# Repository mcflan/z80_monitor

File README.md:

# Z80 Monitor

</img>

A device that allows a host PC to read and write memory on the bus of a Z80
computer (or potentially other CPUs) as well as a few other functions. It makes
use of the Z80's BUSRQ / BUSAK feature to gain access to the bus while the CPU
is running. The circuit is based on an Atmel atmega1281. The host interface is
a bidirectional TTL-level serial (UART) connection that uses a simple hex-based
protocol to control the monitor and provide handshaking. The host interface is
electrically isolated to allow the target device to be power-cycled properly
without being back-powered by the serial signals. This also avoids any risk of
SCR latch-up.

## Host Connector

This is 6-way single-row header to fit a standard FTDI FT232 serial cable (TTL type.) It will work with the 5V and 3V3 versions.

 | Number | Function      |
 |:------:|:------------- |
 |  6     | Not Used      |
 |  5     | Serial Out    |
 |  4     | Serial In     |
 |  3     | Power In      |
 |  2     | Not Used      |
 |  1     | Ground        |

## Bus Connector

See the [pinout file](bus_pinout.md)

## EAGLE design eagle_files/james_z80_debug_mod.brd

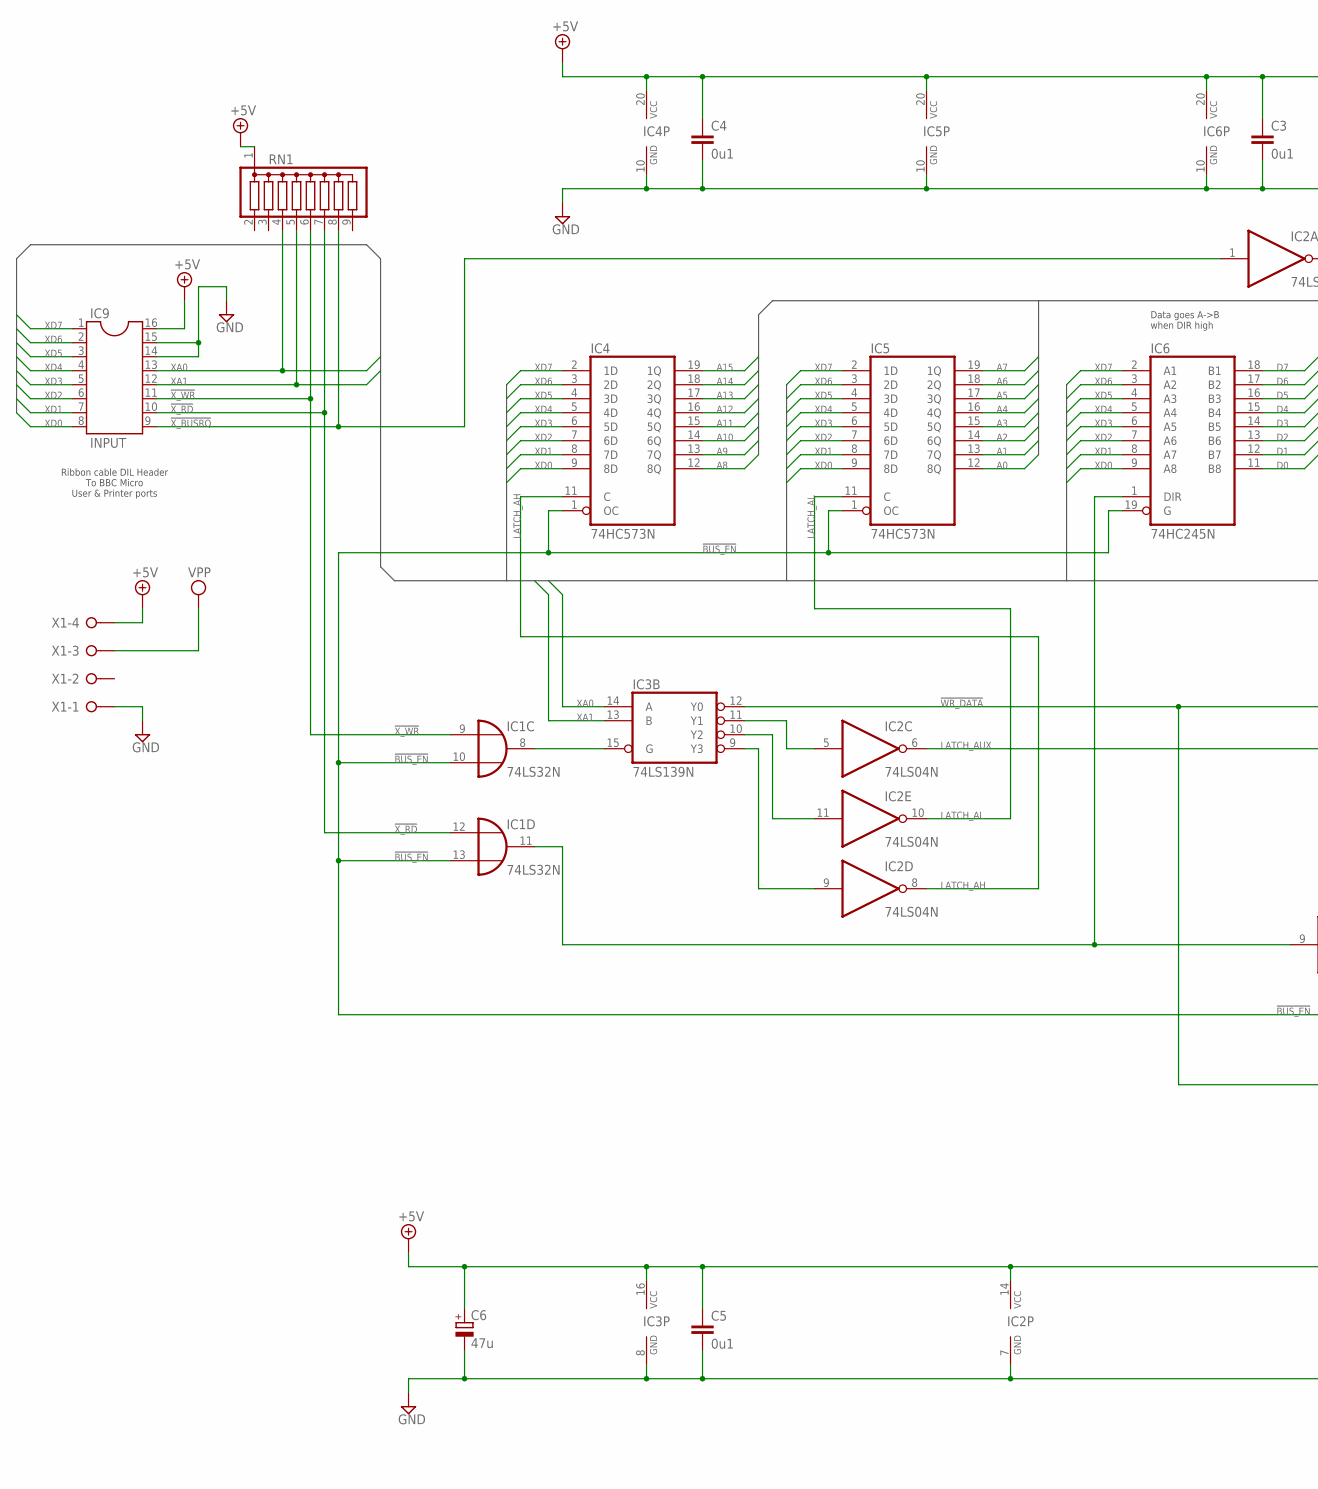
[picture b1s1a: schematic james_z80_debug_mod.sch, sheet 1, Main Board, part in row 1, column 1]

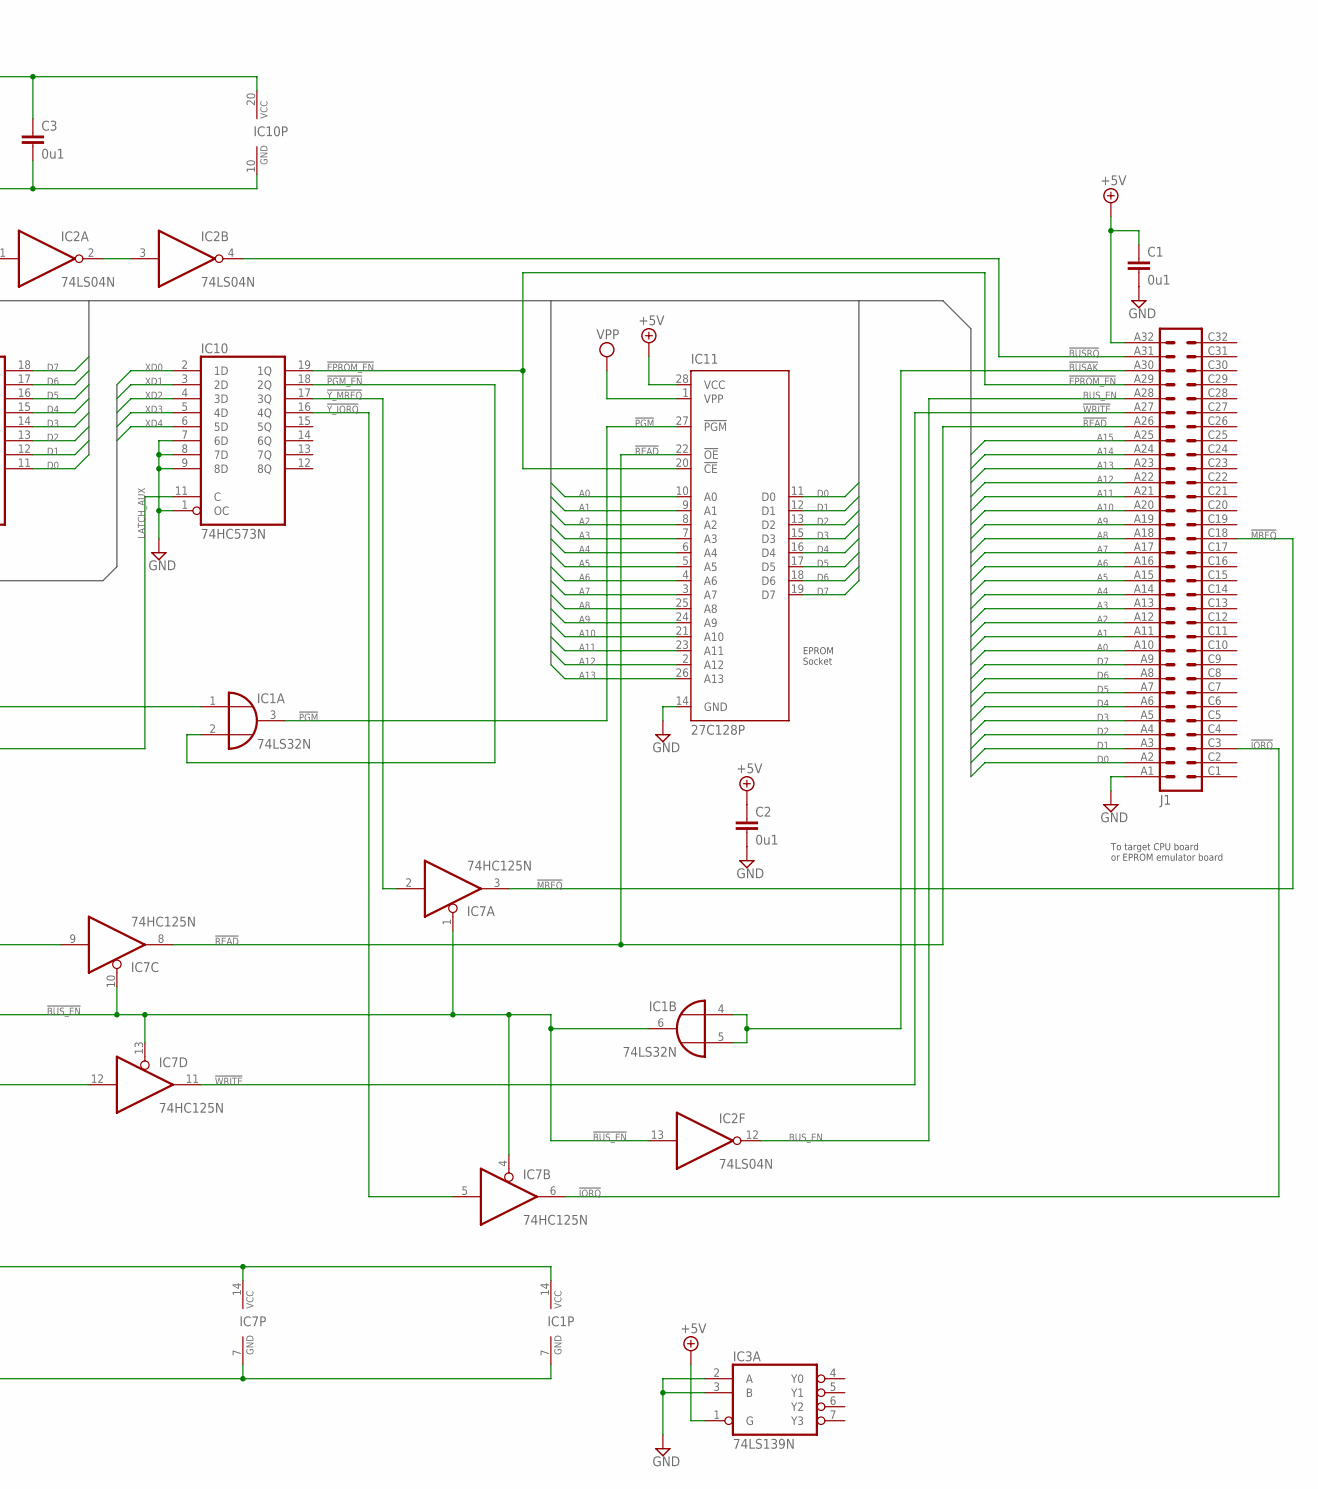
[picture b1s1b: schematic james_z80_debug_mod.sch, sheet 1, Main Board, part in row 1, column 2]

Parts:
C1, C2, C3, C4, C5: 0u1; C025-024X044
C6: 47u; E2,5-5
IC1: 74LS32N; DIL14
IC2: 74LS04N; DIL14
IC3: 74LS139N; DIL16
IC4, IC5, IC10: 74HC573N; DIL20
IC6: 74HC245N; DIL20
IC7: 74HC125N; DIL14
IC9: INPUT; DIL16
IC11: 27C128P; DIL28-6
J1: VG64B
RN1: G08R; SIL9
X1: W237-04P; W237-4P

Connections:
!BUSAK: IC1.4 (I0), IC1.5 (I1), J1.A30
!BUSRQ: IC2.4 (O), J1.A31
!BUS_EN: IC1.6 (O), IC1.10 (I1), IC1.13 (I1), IC2.13 (I), IC4.1 (OC), IC5.1 (OC), IC6.19 (G), IC7.1 (OE), IC7.4 (OE), IC7.10 (OE), IC7.13 (OE)
!EPROM_EN: IC10.19 (1Q), IC11.20 (!CE), J1.A29; also elsewhere on the board
!IORQ: IC7.6 (O), J1.C3
!MREQ: IC7.3 (O), J1.C18
!PGM: IC1.3 (O), IC11.27 (!PGM)
!PGM_EN: IC1.2 (I1), IC10.18 (2Q)
!READ: IC7.8 (O), IC11.22 (!OE), J1.A26; also elsewhere on the board
!WRITE: IC7.11 (O), J1.A27; also elsewhere on the board
!WR_DATA: IC1.1 (I0), IC3.12 (Y0), IC7.12 (I)
!X_BUSRQ: IC2.1 (I), IC9.9, RN1.8
!X_RD: IC1.12 (I0), IC9.10, RN1.7
!X_WR: IC1.9 (I0), IC9.11, RN1.6
!Y_IORQ: IC7.5 (I), IC10.16 (4Q)
!Y_MREQ: IC7.2 (I), IC10.17 (3Q)
+5V: C1.1, C2.1, C3.1, C4.1, C5.1, C6.+, IC1.14 (VCC), IC2.14 (VCC), IC3.1 (G), IC3.16 (VCC), IC4.20 (VCC), IC5.20 (VCC), IC6.20 (VCC), IC7.14 (VCC), IC9.16, IC10.20 (VCC), IC11.28 (VCC), J1.A32, RN1.1, X1.4; also elsewhere on the board
A0: IC5.12 (8Q), IC11.10 (A0), J1.A10; also elsewhere on the board
A1: IC5.13 (7Q), IC11.9 (A1), J1.A11; also elsewhere on the board
A2: IC5.14 (6Q), IC11.8 (A2), J1.A12; also elsewhere on the board
A3: IC5.15 (5Q), IC11.7 (A3), J1.A13; also elsewhere on the board
A4: IC5.16 (4Q), IC11.6 (A4), J1.A14; also elsewhere on the board
A5: IC5.17 (3Q), IC11.5 (A5), J1.A15; also elsewhere on the board
A6: IC5.18 (2Q), IC11.4 (A6), J1.A16; also elsewhere on the board
A7: IC5.19 (1Q), IC11.3 (A7), J1.A17; also elsewhere on the board
A8: IC4.12 (8Q), IC11.25 (A8), J1.A18; also elsewhere on the board
A9: IC4.13 (7Q), IC11.24 (A9), J1.A19; also elsewhere on the board
A10: IC4.14 (6Q), IC11.21 (A10), J1.A20; also elsewhere on the board
A11: IC4.15 (5Q), IC11.23 (A11), J1.A21; also elsewhere on the board
A12: IC4.16 (4Q), IC11.2 (A12), J1.A22; also elsewhere on the board
A13: IC4.17 (3Q), IC11.26 (A13), J1.A23; also elsewhere on the board
A14: IC4.18 (2Q), J1.A24; also elsewhere on the board
A15: IC4.19 (1Q), J1.A25; also elsewhere on the board
BUS_EN: IC2.12 (O), J1.A28; also elsewhere on the board
D0: IC6.11 (B8), IC11.11 (D0), J1.A2; also elsewhere on the board
D1: IC6.12 (B7), IC11.12 (D1), J1.A3; also elsewhere on the board
D2: IC6.13 (B6), IC11.13 (D2), J1.A4; also elsewhere on the board
D3: IC6.14 (B5), IC11.15 (D3), J1.A5; also elsewhere on the board
D4: IC6.15 (B4), IC11.16 (D4), J1.A6; also elsewhere on the board
D5: IC6.16 (B3), IC11.17 (D5), J1.A7; also elsewhere on the board
D6: IC6.17 (B2), IC11.18 (D6), J1.A8; also elsewhere on the board
D7: IC6.18 (B1), IC11.19 (D7), J1.A9; also elsewhere on the board
GND: C1.2, C2.2, C3.2, C4.2, C5.2, C6.-, IC1.7 (GND), IC2.7 (GND), IC3.2 (A), IC3.3 (B), IC3.8 (GND), IC4.10 (GND), IC5.10 (GND), IC6.10 (GND), IC7.7 (GND), IC9.14, IC9.15, IC10.1 (OC), IC10.7 (6D), IC10.8 (7D), IC10.9 (8D), IC10.10 (GND), IC11.14 (GND), J1.A1, X1.1; also elsewhere on the board
LATCH_AH: IC2.8 (O), IC4.11 (C)
LATCH_AL: IC2.10 (O), IC5.11 (C)
LATCH_AUX: IC2.6 (O), IC10.11 (C)
unnamed: IC2.2 (O), IC2.3 (I)
unnamed: IC1.8 (O), IC3.15 (G)
unnamed: IC1.11 (O), IC6.1 (DIR), IC7.9 (I)
unnamed: IC2.5 (I), IC3.11 (Y1)
unnamed: IC2.11 (I), IC3.10 (Y2)
unnamed: IC2.9 (I), IC3.9 (Y3)
VPP: IC11.1 (VPP), X1.3
XA0: IC3.14 (A), IC9.13, RN1.4
XA1: IC3.13 (B), IC9.12, RN1.5
XD0: IC4.9 (8D), IC5.9 (8D), IC6.9 (A8), IC9.8, IC10.2 (1D)
XD1: IC4.8 (7D), IC5.8 (7D), IC6.8 (A7), IC9.7, IC10.3 (2D)
XD2: IC4.7 (6D), IC5.7 (6D), IC6.7 (A6), IC9.6, IC10.4 (3D)
XD3: IC4.6 (5D), IC5.6 (5D), IC6.6 (A5), IC9.5, IC10.5 (4D)
XD4: IC4.5 (4D), IC5.5 (4D), IC6.5 (A4), IC9.4, IC10.6 (5D)
XD5: IC4.4 (3D), IC5.4 (3D), IC6.4 (A3), IC9.3
XD6: IC4.3 (2D), IC5.3 (2D), IC6.3 (A2), IC9.2
XD7: IC4.2 (1D), IC5.2 (1D), IC6.2 (A1), IC9.1

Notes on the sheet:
Ribbon cable DIL Header To BBC Micro User & Printer ports
Data goes A->B when DIR high
EPROM Socket
To target CPU board or EPROM emulator board

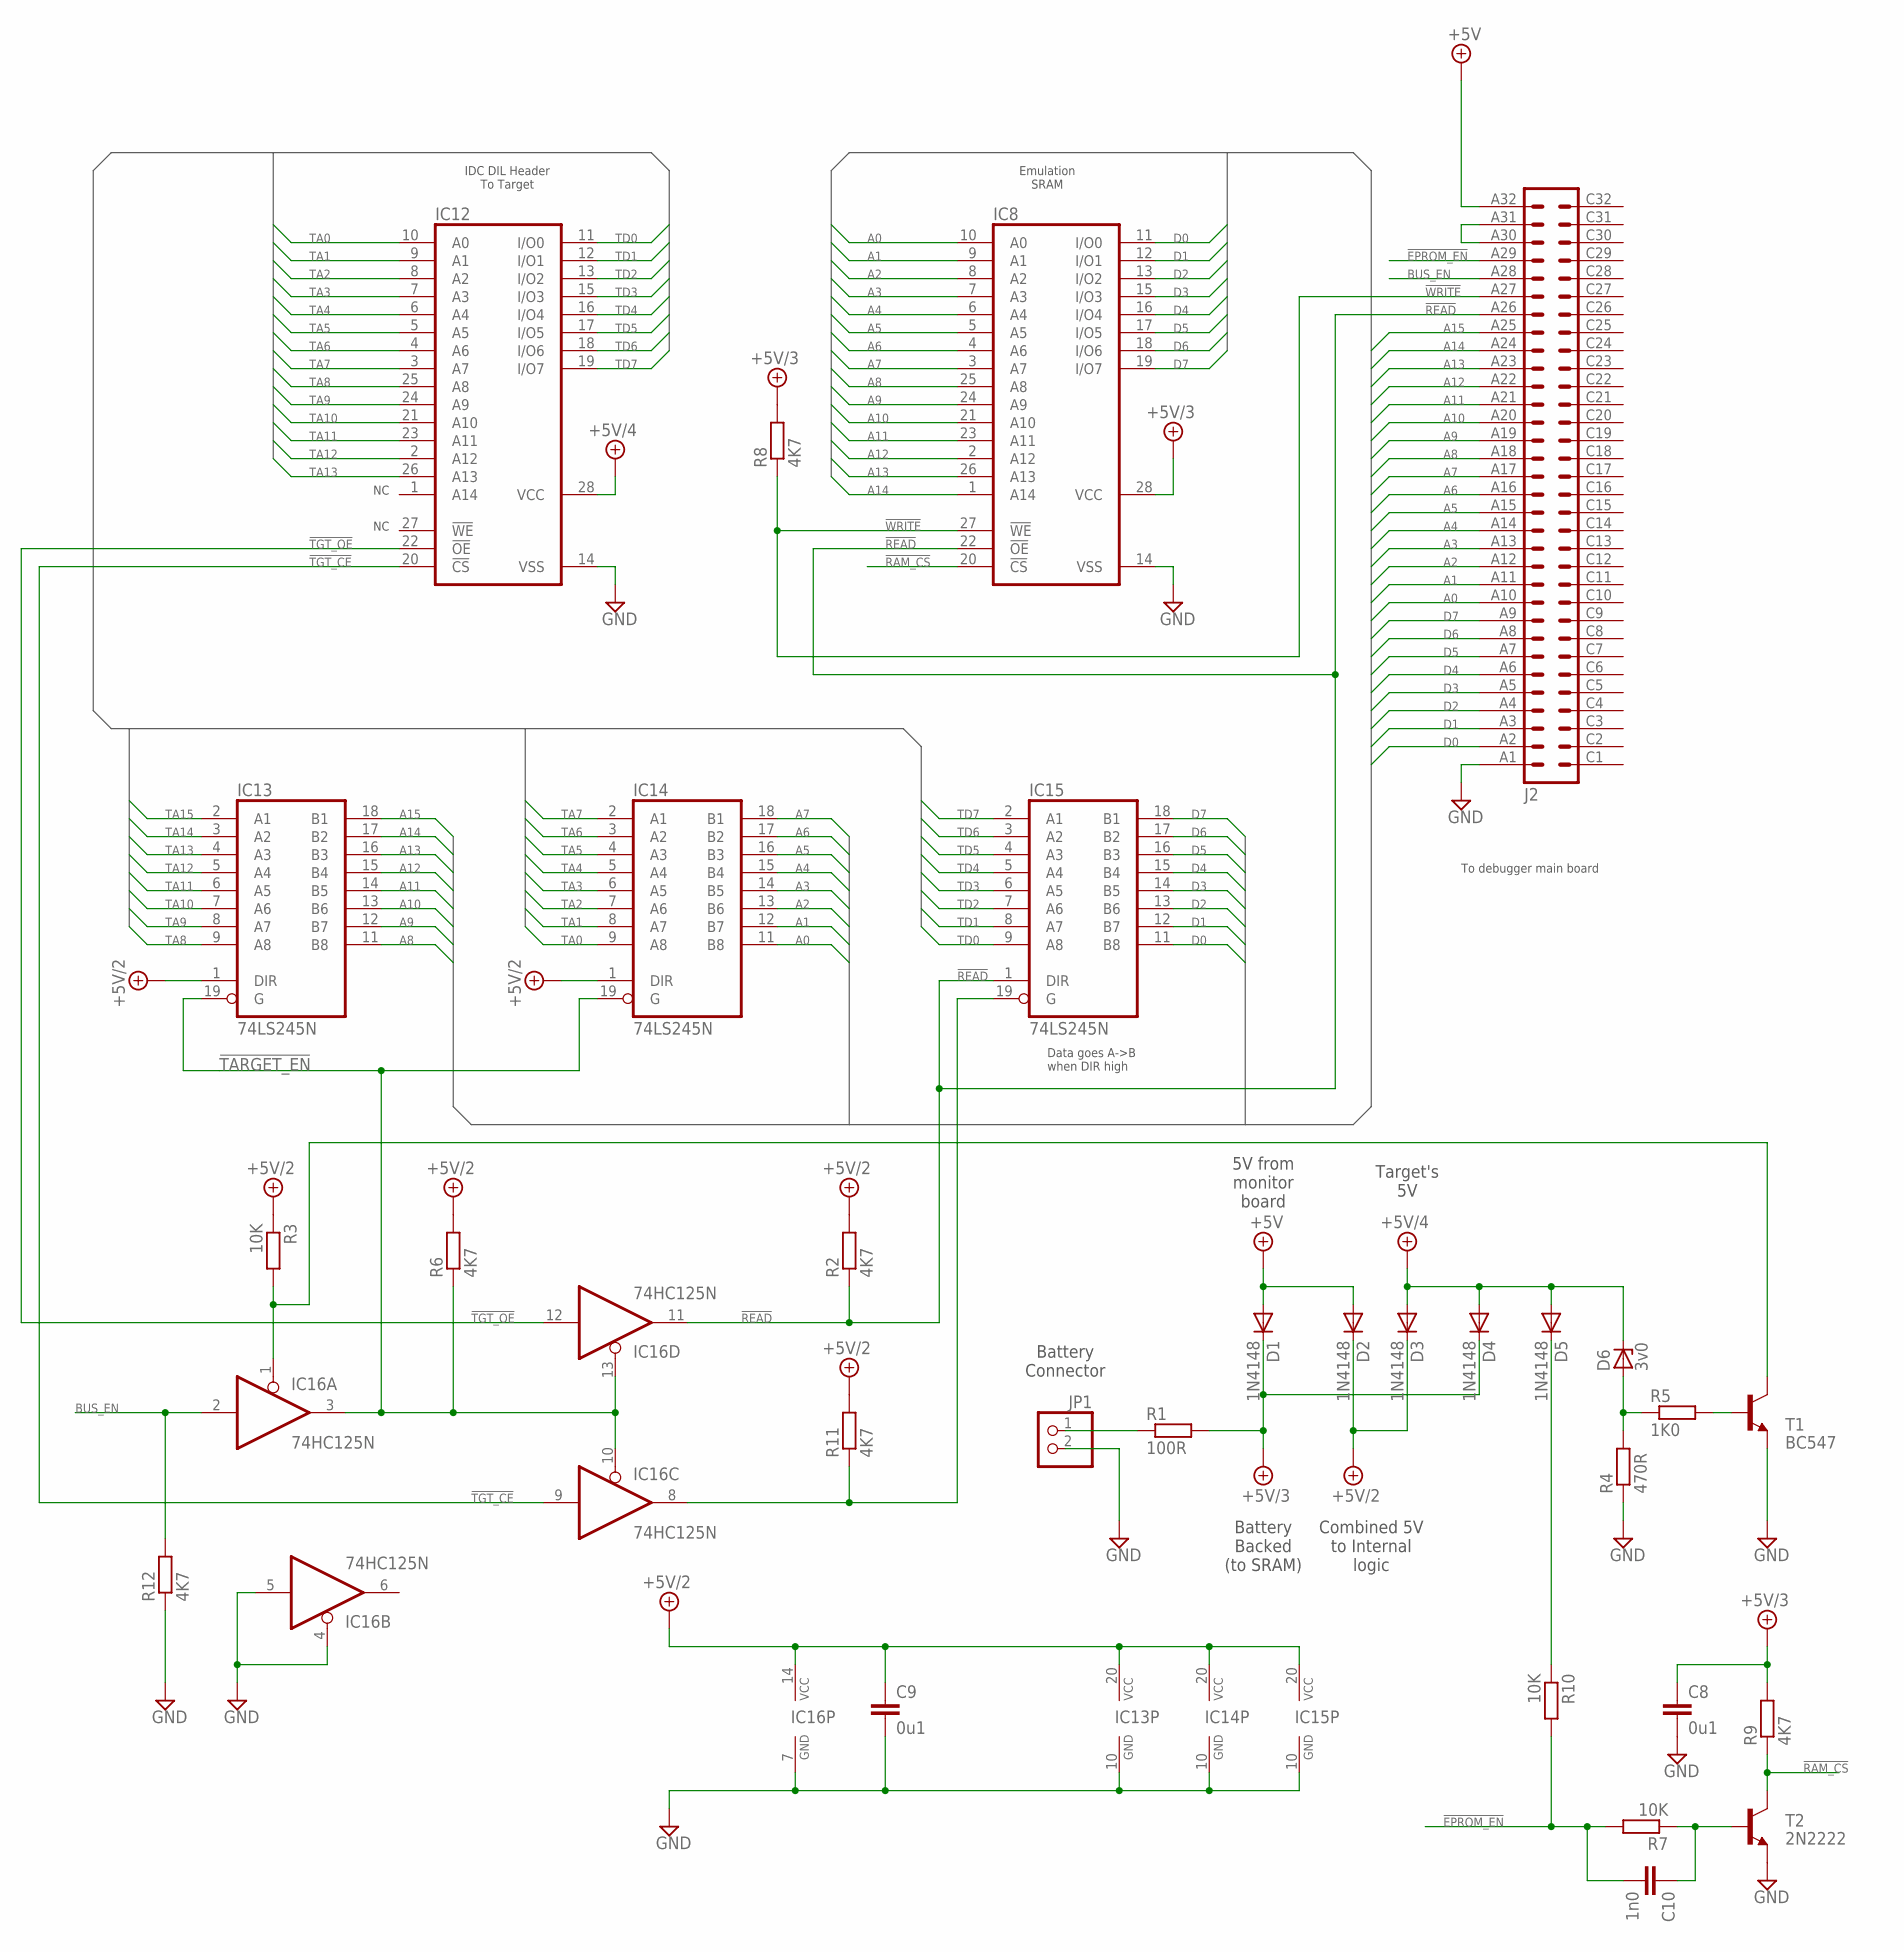
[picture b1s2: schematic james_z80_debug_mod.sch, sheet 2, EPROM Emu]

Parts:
C8, C9: 0u1; C025-024X044
C10: 1n0; C025-024X044
D1, D2, D3, D4, D5: 1N4148; DO35-7
D6: 3v0; F126Z10
IC8, IC12: 62256P; DIL28-6
IC13, IC14, IC15: 74LS245N; DIL20
IC16: 74HC125N; DIL14
J2: VG64B
JP1: PINHD-1X2; 1X02
R1: 100R; 0207/10
R2: 4K7; 0207/10
R3: 10K; 0207/2V
R4: 470R; 0207/10
R5: 1K0; 0207/5V
R6: 4K7; 0204/7
R7: 10K; 0207/5V
R8, R9, R11: 4K7; 0207/2V
R10: 10K; 0207/10
R12: 4K7; 0207/5V
T1: BC547; TO92
T2: 2N2222; TO18

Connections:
!EPROM_EN: C10.2, J2.A29, R7.2, R10.2; also elsewhere on the board
!RAM_CS: IC8.20 (!CS), R9.1, T2.3 (C)
!READ: IC8.22 (!OE), IC15.1 (DIR), IC16.11 (O), J2.A26, R2.1; also elsewhere on the board
!TARGET_EN: IC13.19 (G), IC14.19 (G), IC16.3 (O), IC16.10 (OE), IC16.13 (OE), R6.1
!TGT_CE: IC12.20 (!CS), IC16.9 (I)
!TGT_OE: IC12.22 (!OE), IC16.12 (I)
!WRITE: IC8.27 (!WE), J2.A27, R8.1; also elsewhere on the board
+5V: D1.A, D2.A, J2.A32; also elsewhere on the board
+5V/2: C9.1, D2.C, D3.C, IC13.1 (DIR), IC13.20 (VCC), IC14.1 (DIR), IC14.20 (VCC), IC15.20 (VCC), IC16.14 (VCC), R2.2, R3.1, R6.2, R11.2
+5V/3: C8.1, D1.C, D4.C, IC8.28 (VCC), R1.2, R8.2, R9.2
+5V/4: D3.A, D4.A, D5.A, D6.C, IC12.28 (VCC)
A0: IC8.10 (A0), IC14.11 (B8), J2.A10; also elsewhere on the board
A1: IC8.9 (A1), IC14.12 (B7), J2.A11; also elsewhere on the board
A2: IC8.8 (A2), IC14.13 (B6), J2.A12; also elsewhere on the board
A3: IC8.7 (A3), IC14.14 (B5), J2.A13; also elsewhere on the board
A4: IC8.6 (A4), IC14.15 (B4), J2.A14; also elsewhere on the board
A5: IC8.5 (A5), IC14.16 (B3), J2.A15; also elsewhere on the board
A6: IC8.4 (A6), IC14.17 (B2), J2.A16; also elsewhere on the board
A7: IC8.3 (A7), IC14.18 (B1), J2.A17; also elsewhere on the board
A8: IC8.25 (A8), IC13.11 (B8), J2.A18; also elsewhere on the board
A9: IC8.24 (A9), IC13.12 (B7), J2.A19; also elsewhere on the board
A10: IC8.21 (A10), IC13.13 (B6), J2.A20; also elsewhere on the board
A11: IC8.23 (A11), IC13.14 (B5), J2.A21; also elsewhere on the board
A12: IC8.2 (A12), IC13.15 (B4), J2.A22; also elsewhere on the board
A13: IC8.26 (A13), IC13.16 (B3), J2.A23; also elsewhere on the board
A14: IC8.1 (A14), IC13.17 (B2), J2.A24; also elsewhere on the board
A15: IC13.18 (B1), J2.A25; also elsewhere on the board
BUS_EN: IC16.2 (I), J2.A28, R12.2; also elsewhere on the board
D0: IC8.11 (I/O0), IC15.11 (B8), J2.A2; also elsewhere on the board
D1: IC8.12 (I/O1), IC15.12 (B7), J2.A3; also elsewhere on the board
D2: IC8.13 (I/O2), IC15.13 (B6), J2.A4; also elsewhere on the board
D3: IC8.15 (I/O3), IC15.14 (B5), J2.A5; also elsewhere on the board
D4: IC8.16 (I/O4), IC15.15 (B4), J2.A6; also elsewhere on the board
D5: IC8.17 (I/O5), IC15.16 (B3), J2.A7; also elsewhere on the board
D6: IC8.18 (I/O6), IC15.17 (B2), J2.A8; also elsewhere on the board
D7: IC8.19 (I/O7), IC15.18 (B1), J2.A9; also elsewhere on the board
GND: C8.2, C9.2, IC8.14 (VSS), IC12.14 (VSS), IC13.10 (GND), IC14.10 (GND), IC15.10 (GND), IC16.4 (OE), IC16.5 (I), IC16.7 (GND), J2.A1, JP1.2, R4.1, R12.1, T1.1 (E), T2.1 (E); also elsewhere on the board
unnamed: D6.A, R4.2, R5.1
unnamed: IC16.1 (OE), R3.2, T1.3 (C)
unnamed: J2.A30, J2.A31
unnamed: IC15.19 (G), IC16.8 (O), R11.1
unnamed: JP1.1, R1.1
unnamed: R5.2, T1.2 (B)
unnamed: C10.1, R7.1, T2.2 (B)
unnamed: D5.C, R10.1
TA0: IC12.10 (A0), IC14.9 (A8)
TA1: IC12.9 (A1), IC14.8 (A7)
TA2: IC12.8 (A2), IC14.7 (A6)
TA3: IC12.7 (A3), IC14.6 (A5)
TA4: IC12.6 (A4), IC14.5 (A4)
TA5: IC12.5 (A5), IC14.4 (A3)
TA6: IC12.4 (A6), IC14.3 (A2)
TA7: IC12.3 (A7), IC14.2 (A1)
TA8: IC12.25 (A8), IC13.9 (A8)
TA9: IC12.24 (A9), IC13.8 (A7)
TA10: IC12.21 (A10), IC13.7 (A6)
TA11: IC12.23 (A11), IC13.6 (A5)
TA12: IC12.2 (A12), IC13.5 (A4)
TA13: IC12.26 (A13), IC13.4 (A3)
TA14: IC13.3 (A2)
TA15: IC13.2 (A1)
TD0: IC12.11 (I/O0), IC15.9 (A8)
TD1: IC12.12 (I/O1), IC15.8 (A7)
TD2: IC12.13 (I/O2), IC15.7 (A6)
TD3: IC12.15 (I/O3), IC15.6 (A5)
TD4: IC12.16 (I/O4), IC15.5 (A4)
TD5: IC12.17 (I/O5), IC15.4 (A3)
TD6: IC12.18 (I/O6), IC15.3 (A2)
TD7: IC12.19 (I/O7), IC15.2 (A1)

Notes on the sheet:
To debugger main board
Emulation SRAM
IDC DIL Header To Target
Data goes A->B when DIR high
5V from monitor board
Battery Backed (to SRAM)
Combined 5V to Internal logic
Target's 5V
Battery Connector

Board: 2 copper layers, 50 parts (0 on the bottom side), 100 nets, no tracks yet.

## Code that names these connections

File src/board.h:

#ifndef BOARD_H
#define BOARD_H

/* CPU frequency */
#define F_CPU 16000000UL

#include <avr/io.h>

#define COM_CDEV                   (UART1_CDEV)

/* timing */

/* Main timer - 100 Hz */
#define TIMER1_PRESCALE             (8)
#define TIMER1_RATE                 (100)
#define TIMER1_RELOAD               (F_CPU/TIMER1_PRESCALE/TIMER1_RATE)

#define RATE(x) (x * TIMER1_RATE)


/* soft timer designations */
#define ST_UART                     (0)
#define ST_WAIT                     (1)
#define ST_LED                      (2)
#define ST_FIX                      (3)


/* I/O pins */
#define AL_PORT                     (PORTA)
#define AL_DDR                      (DDRA)
#define AH_PORT                     (PORTF)
#define AH_DDR                      (DDRF)

#define DA_PORT                     (PORTC)
#define DA_PIN                      (PINC)
#define DA_DDR                      (DDRC)

#define CTRL_PORT                   (PORTD)
#define CTRL_PIN                    (PIND)
#define CTRL_DDR                    (DDRD)

#define IORQ                        (1 << PD0)
#define MREQ                        (1 << PD1)
#define RXD1                        (1 << PD2)
#define TXD1                        (1 << PD3)
#define RD                          (1 << PD4)
#define WR                          (1 << PD5)
#define M1                          (1 << PD6)
#define RESET                       (1 << PD7)

#define RSVD0                       (1 << PE2)
#define BUSRQ                       (1 << PE3)
#define BUSAK                       (1 << PE4)
#define HALT                        (1 << PE5)
#define RSVD1                       (1 << PE6)
#define RSVD2                       (1 << PE7)

#define WAIT                        (1 << PG0)
#define INT                         (1 << PG1)
#define NMI                         (1 << PG5)

#define LEDS_NUMOF                  (1)
#define LED_PORT                    (PORTB)
#define COMS_LED                    (0)
#define COMS_LED_PIN                (4)


enum {
    MEM_TYPE_MEM = 0,
    MEM_TYPE_IO = 1,
};



/* ADC - Vref is set by an external reference as of PCB Rev.4 */
#define VREF                        (2.500)
#define ADC_BITS                    (10)
/* divide by 64, which gives 125KHz ADC clock for 8MHZ xtal */
#define ADC_CLOCK_DIVIDER (6)

char sleep_read(int fd, int timeout);

#endif /* BOARD_H */

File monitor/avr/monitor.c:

/*
 * Z80 Monitor board driver
 *
 * (C) Copyright James L Macfarlane, Airborne Engineering Ltd 2020.
 */

#include "board.h"

#include <avr/io.h>
#include <avr/interrupt.h>
#include <util/delay.h>
#include <avr/io.h>
#include <avr/sleep.h>
#include <avr/pgmspace.h>
#include <avr/eeprom.h>
#include <avr/sleep.h>
#include <avr/cpufunc.h>

#include <stdlib.h>
#include <string.h>
#include <ctype.h>
#include <stdio.h>
#include <math.h>

#include "uart.h"
#include "timer.h"
#include "debug.h"
#include "hexify.h"
#include "poll.h"
#include "monitor.h"

hexify_encoder_t henc;
hexify_decoder_t hdec;

#if defined(GIT_VERSION) && defined(GIT_DATE)
/* Version message */
    #define VERSION_MSG  "# Firmware git hash " GIT_VERSION " " GIT_DATE " Build " __DATE__ " " __TIME__ "\n\n\r"
#else
    #error "GIT_VERSION and/or GIT_DATE not defined."
#endif

#ifdef DEBUG
    uint8_t debug_lvl = 1;
#endif


/*
 * Sleep a number of seconds using interrupt-driven timer.
 */
void wait(float t)
{
    timer_start(ST_WAIT, TIMER_MODE_ONESHOT, RATE(t));
    timer_sleep(ST_WAIT);
}

hexify_decoder_t decoder;


static inline void set_reg_addr(uint8_t x)
{
    PORTC &= ~0x03;
    PORTC |= x & 0x03;
    _NOP(); _NOP(); _NOP(); _NOP();
}

static inline void write(uint8_t x)
{
    DDRD = 0xfc;
    DDRB = 0x03;
    PORTD = x;
    PORTB = x & 3;
    PORTC &= ~NX_WR; // Assert write line
    _NOP(); _NOP(); _NOP(); _NOP(); _NOP(); _NOP();
    PORTC |= NX_WR; // De-assert write line
    _NOP(); _NOP(); _NOP(); _NOP(); _NOP(); _NOP();
}

static inline void write_reg(uint8_t reg_addr, uint8_t x)
{
    set_reg_addr(reg_addr);
    write(x);
}

static inline void write_control(uint8_t x)
{
    write_reg(REG_CONTROL, x);
}

static inline void write_address(uint16_t x)
{
    write_reg(REG_ADDR_L, x & 0xff);
    write_reg(REG_ADDR_H, x >> 8);
}

static inline void write_data(uint8_t x)
{
    write_reg(REG_DATA, x);
}

static inline uint8_t read_data(void)
{
    // Set port direction to input
    DDRD = 0;
    DDRB = 0;
    PORTC &= ~NX_RD; // Assert read line
    _NOP(); _NOP(); _NOP(); _NOP(); _NOP(); _NOP();
    uint8_t x = (PIND & 0xfc) | (PINB & 0x03);
    PORTC |= NX_RD; // De-assert read line
    _NOP(); _NOP(); _NOP(); _NOP(); _NOP(); _NOP();
    return x;
}

static inline void claim_bus(void)
{

    PORTC &= ~NX_BUSRQ; // Assert bus request line
}


static inline void release_bus(void)
{
    PORTC |= NX_BUSRQ; // De-assert bus request line
}


static inline void write_block(uint16_t addr, uint8_t *data, int size)
{
    int i;
    for (i = 0; i < size; i++) {
        write_address(addr++);
        write_data(data[i]);
    }
}

static inline void read_block(uint16_t addr, uint8_t *data, int size)
{
    int i;
    for (i = 0; i < size; i++) {
        write_address(addr++);
        data[i] = read_data();
    }
}

typedef struct mon_s {
    uint16_t addr;
    uint8_t bus_claimed;
    uint8_t view_on;
    uint8_t inc_addr;
    uint8_t mem_type;
    int cmd;
    int count;
    int buf_ptr;
} mon_t;

void update_hardware(mon_t *mon)
{
    if (mon->bus_claimed) {
        claim_bus();
    } else {
        release_bus();
    }
    if (mon->mem_type == 0) write_control(~CTRL_MREQ);
    if (mon->mem_type == 1) write_control(~CTRL_IORQ);

}

static void set_memtype(uint8_t memtype)
{
    if (memtype == 0) write_control(~CTRL_MREQ);
    if (memtype == 1) write_control(~CTRL_IORQ);
}

void mon_init(mon_t *mon)
{
    mon->inc_addr = 0;
    mon->bus_claimed = 0;
    mon->mem_type = 0; // Default to main memory
    mon->buf_ptr = 0;
}

#define RD_BUF_SIZE     (32)
static uint8_t rd_buf[RD_BUF_SIZE];

void do_msg(mon_t *mon, uint8_t type, int len, uint8_t *data)
{
    switch (type) {
        case MSG_WR: {
            // type(1), memtype(1), address(2), data(N), checksum(1)
            int size = len - 3;
            if (size < 0) {
                printf("# Not enough bytes (%d) for message type %d\n", len, type);
                break;
            }
            uint8_t memtype = data[0];
            set_memtype(memtype);
            uint16_t addr = data[1] | (data[2] << 8);
            printf("# Writing %2d bytes at 0x%04X - ", size, addr);
            write_block(addr, data+3, size);
            read_block(addr, rd_buf, size);
            int i;
            for (i = 0; i < size; i++) {
                if ((data+3)[i] != rd_buf[i]) break;
            }
            if (i < size) {
                printf("Error at 0x%04X\n", addr+i);
            } else {
                printf("ok\n");
            }
            break;
        }
        case MSG_RD: {
            uint8_t memtype = data[0];
            set_memtype(memtype);
            uint16_t addr = data[1] | (data[2] << 8);
            int size = data[3];
            if (size > (RD_BUF_SIZE-2)) {
                printf("# Can't read more than %d bytes at a time\n", RD_BUF_SIZE-2);
                break;
            }
            rd_buf[0] = addr & 0xff;
            rd_buf[1] = addr >> 8;
            read_block(addr, rd_buf+2, size);
            hexify_sender_start(&henc, MSG_RD, rd_buf, size+2);
            char c;
            while  (hexify_sender_next(&henc, &c)) cdev_put(EXT_CDEV, c);
            break;
        }
        case MSG_BUS_REQ:
            printf("# Acquire bus\n");
            claim_bus();
            break;
        case MSG_BUS_REL:
            printf("# Release bus\n");
            release_bus();
            break;
        default:
            printf("# Don't know about msg type %2d\n", type);
    }
}

#define MSG_BUF_SIZE     (64)
static uint8_t msgbuf[MSG_BUF_SIZE];

static void main_loop(mon_t *mon)
{
    mon_init(mon);
    update_hardware(mon);
    hexify_recvr_init(&hdec, msgbuf, MSG_BUF_SIZE);
    // Wait for a message to arrive then process it
    while (1) {
        uint8_t type;
        int len;
        char c = cdev_get(EXT_CDEV);
        int ret = hexify_recvr_next(&hdec, c, &type, &len);
        if (ret == 0) {
            do_msg(mon, type, len, msgbuf);
        }
        if (ret < 0) {
            printf("# Hex encoding error %d\n", ret);
        }
    }
}

static mon_t mon;

int main(void)
{
    /*
     * XD[7:2] => PD[7..2], tri-state
     * (PD1 an PD0 used for serial I/F)
     * XD[1..0] => PB[1..], tri-state
     * XA[1..0] => PC[1..0], output
     * /X_RD => PC2, output
     * /X_WR => PC3, output
     * /X_BUSRQ => PC4, output
     *
     * Address map:
     * 0: Write data
     * 1: Address latch A[7..0]
     * 2: Address latch A[15..8]
     * 3: Control register:
     *      Bit 0: !EPROM_EN
     *      Bit 1: !PGM_EN
     *      Bit 2: !MREQ
     *      Bit 3: !IOREQ
     */

    DDRD = 0xff; // Start as all inputs
    DDRB = 0x03;
    DDRC = 0x1f;
    // Start with control outputs de-asserted (high)
    PORTC |= NX_BUSRQ | NX_WR | NX_RD;

    timer_init(TIMER1_RELOAD);

    /* turn on global interrupts */
    sei();

    uart0_init(EXT_CDEV, 8); /* 115200 baud */
    stdout = &uart0_fp;

    cdev_put(EXT_CDEV, '\n');
    cdev_put(EXT_CDEV, '\r');
    PRINT("MCU Monitor. J.Macfarlane 2020\n\r");
    PRINT(VERSION_MSG);

    //hexify_recvr_init(&decoder, (uint8_t *)&rx_msg, XBEE_MSG_LEN);

    release_bus();

    main_loop(&mon);

    return 0;
}

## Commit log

2020-10-27 Add bus layout.
2020-10-27 More updates.
2020-10-28 More pinout updates.
2020-10-28 Update pinouts.
2020-10-28 Add kicad schematic - still work-in-progress.
2020-10-29 UART section of IO board completed.
2020-10-29 Add ignore files and jm_z80 library.
2020-10-29 Add sym lib table.
2020-10-29 Lots more work on schematic
2020-10-29 Name sheets.
2020-10-29 Un-fsck something which made most of the chips into 74LS00 for some very odd reason. Also start to assign footprints.
2020-10-29 Add chache.lib file to git.
2020-10-30 Re-annotateand fix doubled-up U6 unit.
2020-10-30 Add some no-connection symbols.
2020-10-30 Add dcm file for jm_z80 lib.
2020-10-30 Add missing connection for /wait.
2020-10-30 Add some missing gates and wiring.
2020-10-30 Complete RAM_WR_EN wiring.
2020-10-30 Add pull-up for /IORQ on IO board.
2020-10-30 Add eagle files for old z80 monitor board and for mods to make it compatible with new 50 way pinout.
2020-10-30 Add adapter board for old monitor eurocard connector to new 50 way pinout.
2020-10-31 Add description of new bus pinout specs.
2020-10-31 Trying to get overbar on signal names in markdown.
2020-10-31 More updates to pinout.
2020-10-31 Update monitor mods.
2020-10-31 Update to adapter.
2020-11-05 Add a label to eagle schematics.
2020-11-05 Add beginings of arduino monitor code.
2020-11-10 Just echo characters back for now.
2020-11-10 Starting to implement monitor commands.
2020-11-11 Now imports ihex records.
2020-11-11 Add z80 src examples, etc.
2020-11-11 claim bus before writing a block.
2020-11-11 Update Makefile header.
2020-11-11 Move ihex char parsing into own fn.
2020-11-12 Minor updates.
2020-11-14 Add kicad schematic and rough veroboard layout for raspi floppy interface.
2020-11-14 Add cache lib.
2020-11-16 Add missing resnet for keyboard pull-ups.
2020-11-18 Add freeCAD drawing of spacer.
2020-11-18 Update Pi floppy i/f.
2020-11-18 Minor update to schematic.
2020-11-18 Move mkII schematic dir.
2020-11-18 Add g-code for spacer top machining.
2020-11-18 Fix g2/g3 mix-up and missing o101 call.
2020-11-18 Move src dir.
2020-11-18 Add original Z80 binaries.
2020-11-18 Update README's.
2020-11-18 Fix table in md file.
2020-11-18 Rename a dir.
2020-11-19 Add script for disassembling original Z80 binaries.
2020-11-19 Add chamfer.
2020-11-19 Add tool heights. Fix missing brace.
2020-11-19 Move home pos further out, fix some commented-out g42's
2020-11-19 Fix wrong x dim on foot outline.
2020-11-19 Change move-off cmds.
2020-11-19 Fix #9 - should be radius not dia.
2020-11-20 New approach to roughing.
2020-11-20 Seems that f30 at end of a line affects all following lines.
2020-11-20 Move file.
2020-11-20 Split g-code into a file per tool because linuxCNC won't allow manual touch-off when paused.
2020-11-20 Lots of updates to gcode.
2020-11-20 Typo.
2020-11-21 Increase amount to remove in finishing cut to try to re-cut the chips less.
2020-11-21 Increase feed rate.
2020-11-22 Abstract the feed rate and increase by 50%.
2020-11-22 Fix library path for adapter after moving mkII schematic dir.
2020-11-22 Add note to CPU schematic.
2020-11-23 Add some notes about increasing number of hardware upgrades and fixes to mkII.
2020-11-28 Add some code stubs. serial.asm works, display.asm does not, probably due to hardware issues.
2020-11-28 Update keyb3 disassembly.
2020-11-29 Move monitor AVR to own dir.
2020-11-30 Change of plan: get rid of interactive terminal and instead us code on host. This solves problem of flow-control. Add header for magic numbers shared with host monitor code.
2020-11-30 Add monitor host python code. Can write to mem.
2020-11-30 Minor fixes.
2020-11-30 Edit serial.asm
2020-11-30 Can now read data back from monitor.
2020-11-30 Fix pretty-printing.
2020-11-30 Fix cmd line help.
2020-11-30 Some minor tidying-up of monitor code.
2020-12-01 LCD now working
2020-12-03 Add kicad project for new monitor board.
2020-12-03 Assign some footprints and begin to play with layout
2020-12-03 Add some comments.
2020-12-03 Add new minimalist atmega1281-bases monitor.
2020-12-03 Add gitignore.
2020-12-06 Finished new AVR-based monitor board, pending final checks and gerber generation.
2020-12-06 Move LEDs to edge of board and label. Add 2x M2.5 clearance hole.
2020-12-07 Various updates to board.
2020-12-07 More re-arrangement of files.
2020-12-07 Add README.
2020-12-07 Add pic.
2020-12-07 Image update.
2020-12-07 Add gerbers
2020-12-07 Add src dir. Empty atm.
2020-12-07 Re-do gerbers with new settings.
2020-12-07 Add zip.
2020-12-07 Update gerbers.
2020-12-07 Add pinout.
2020-12-07 Rename pinput file.
2021-01-03 Update LED resistor values to try to match brightness.
2021-01-03 Initial commit of monitor AVR code.
2021-01-03 230400 baud doesn't rx properly. Changed to 115200.
2021-01-04 Add code to flush serial input buf in python. Add reset and release functionality.
2021-01-04 Add snag list for PCB.
2021-01-05 Minor tidy-up of python.
2021-01-05 Add NMI command.
2021-01-06 Add command to clear areas of memory.
2021-01-08 Update snaglist. Add INT function.
2021-02-15 Update board
